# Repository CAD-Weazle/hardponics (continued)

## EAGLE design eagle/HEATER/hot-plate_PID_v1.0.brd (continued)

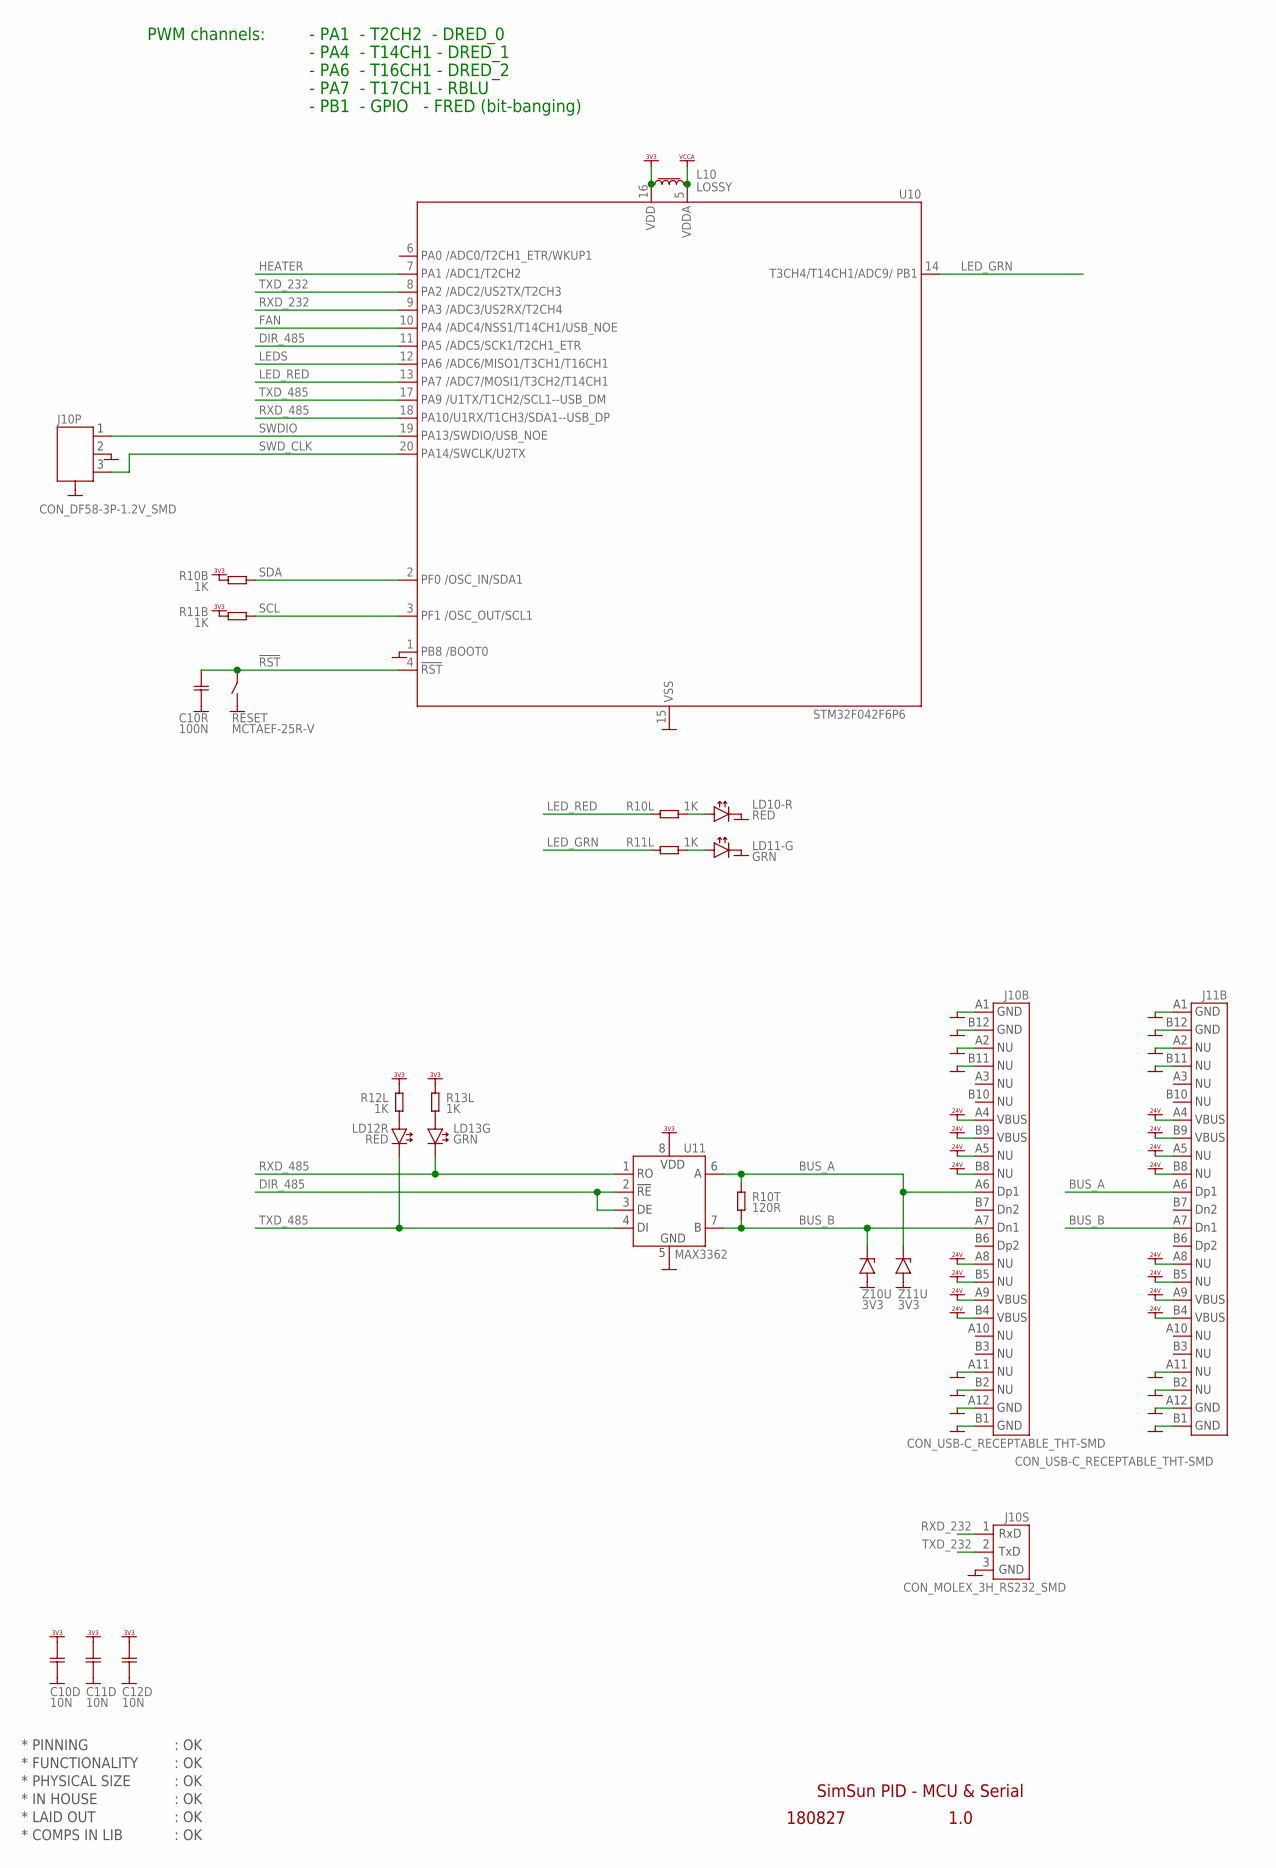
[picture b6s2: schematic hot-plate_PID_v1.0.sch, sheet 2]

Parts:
C10D, C11D, C12D: 10N; CAP0603
C10R: 100N; CAP0603
J10B, J11B: CON_USB-C_RECEPTABLE_THT-SMD
J10P: CON_DF58-3P-1.2V_SMD
J10S: CON_MOLEX_3H_RS232_SMD; CON_MOLEX_3H+SMD
L10: LOSSY; L_0603
LD10-R, LD12R: RED; LED_SMD_0603
LD11-G, LD13G: GRN; LED_SMD_0603
R10B, R10L, R11B, R11L, R12L, R13L: 1K; RES0603
R10T: 120R; RES0603
RESET: MCTAEF-25R-V; SWITCH_SMD_PBUTTON_2P
U10: STM32F042F6P6; TSSOP20
U11: MAX3362; SOT23-8
Z10U, Z11U: 3V3; ZENER_SOD80

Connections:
!RST: C10R.1, RESET.2 (3-4), U10.4 (4.!RST)
BUS_A: J10B.A6 (A6.DP1), J11B.A6 (A6.DP1), R10T.1, U11.6 (6.A), Z11U.2 (-)
BUS_B: J10B.A7 (A7.DN1), J11B.A7 (A7.DN1), R10T.2, U11.7 (7.B), Z10U.2 (-)
DIR_485: U10.11 (11.PA5), U11.2 (2.!RE), U11.3 (3.DE)
FAN: U10.10 (10.PA4); also elsewhere on the board
GND: C10D.2, C10R.2, C11D.2, C12D.2, J10B.A1 (A1.GND), J10B.A2 (A2.NU), J10B.A11 (A11.NU), J10B.A12 (A12.GND), J10B.B1 (B1.GND), J10B.B2 (B2.NU), J10B.B11 (B11.NU), J10B.B12 (B12.GND), J10P.2, J10P.GND1 (4), J10P.GND2 (4), J10S.3, J11B.A1 (A1.GND), J11B.A2 (A2.NU), J11B.A11 (A11.NU), J11B.A12 (A12.GND), J11B.B1 (B1.GND), J11B.B2 (B2.NU), J11B.B11 (B11.NU), J11B.B12 (B12.GND), LD10-R.C, LD11-G.C, RESET.1 (1-2), U10.1 (1.BOOT0), U10.15 (15.GND), U11.5 (5.GND), Z10U.1 (+), Z11U.1 (+); also elsewhere on the board
HEATER: U10.7 (7.PA1); also elsewhere on the board
LEDS: U10.12 (12.PA6); also elsewhere on the board
LED_GRN: R11L.1, U10.14 (14.PB1)
LED_RED: R10L.1, U10.13 (13.PA7)
unnamed: LD11-G.A, R11L.2
unnamed: LD10-R.A, R10L.2
unnamed: LD13G.A, R13L.2
unnamed: LD12R.A, R12L.2
RXD_232: J10S.1, U10.9 (9.PA3)
RXD_485: LD13G.C, U10.18 (18.PA10), U11.1 (1.RO)
SCL: R11B.2, U10.3 (3.OSC_OUT); also elsewhere on the board
SDA: R10B.2, U10.2 (2.OSC_IN); also elsewhere on the board
SWDIO: J10P.1, U10.19 (19.PA13)
SWD_CLK: J10P.3, U10.20 (20.PA14)
TXD_232: J10S.2, U10.8 (8.PA2)
TXD_485: LD12R.C, U10.17 (17.PA9), U11.4 (4.DI)
VCCA: L10.2, U10.5 (5.VDDA)
VDD_3V3: C10D.1, C11D.1, C12D.1, L10.1, R10B.1, R11B.1, R12L.1, R13L.1, U10.16 (16.VDD), U11.8 (8.VDD); also elsewhere on the board
VDD_24V: J10B.A4 (A4.VBUS), J10B.A5 (A5.NU), J10B.A8 (A8.NU), J10B.A9 (A9.VBUS), J10B.B4 (B4.VBUS), J10B.B5 (B5.NU), J10B.B8 (B8.NU), J10B.B9 (B9.VBUS), J11B.A4 (A4.VBUS), J11B.A5 (A5.NU), J11B.A8 (A8.NU), J11B.A9 (A9.VBUS), J11B.B4 (B4.VBUS), J11B.B5 (B5.NU), J11B.B8 (B8.NU), J11B.B9 (B9.VBUS); also elsewhere on the board

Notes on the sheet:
* PINNING
* FUNCTIONALITY
* PHYSICAL SIZE
* LAID OUT
* COMPS IN LIB
* IN HOUSE
: OK
SimSun PID - MCU & Serial
180827
1.0
PWM channels:
- PA1 - T2CH2 - DRED_0
- PA4 - T14CH1 - DRED_1
- PA6 - T16CH1 - DRED_2
- PA7 - T17CH1 - RBLU
- PB1 - GPIO - FRED (bit-banging)

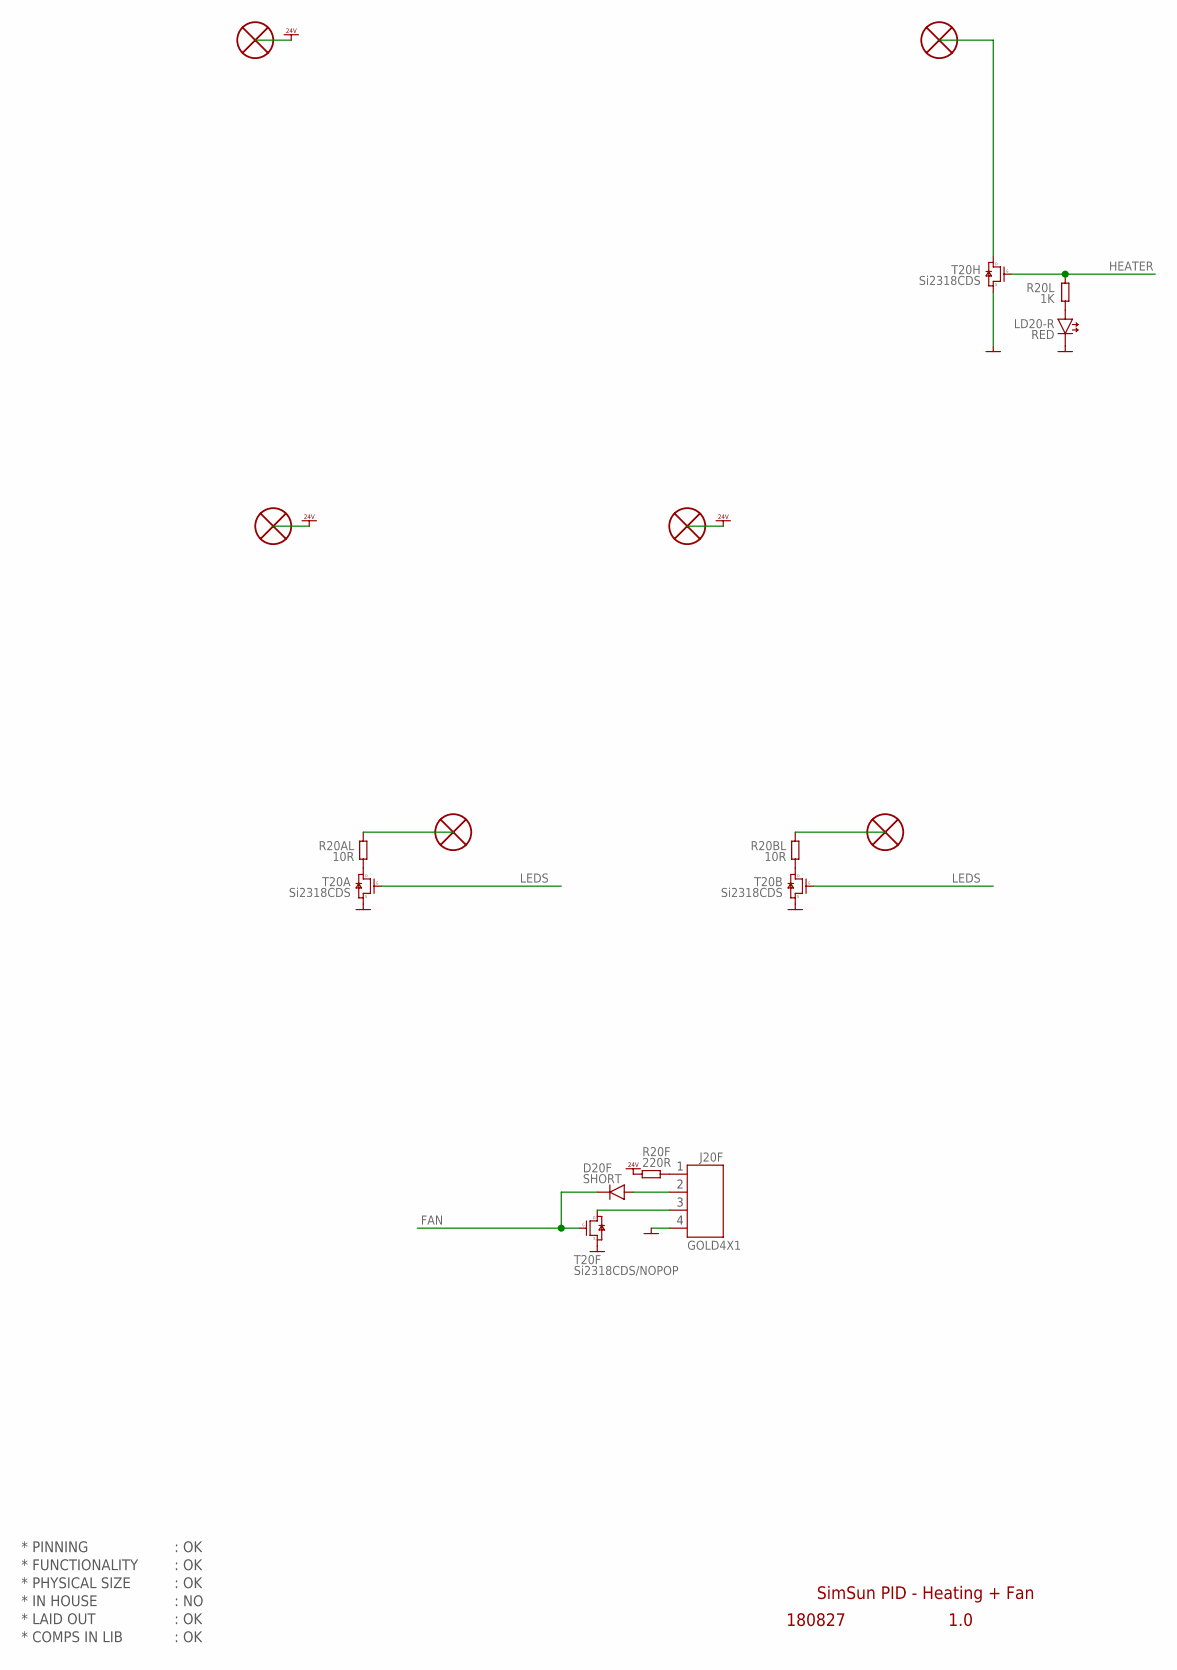
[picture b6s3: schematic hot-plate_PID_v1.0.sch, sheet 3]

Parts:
D20F: SHORT; DIODE_SOD323
H5, H6, H10, H15, H16, H17: HOLE_PTH_1.0MM
J20F: GOLD4X1
LD20-R: RED; LED_SMD_0603
R20AL, R20BL: 10R; RES0603
R20F: 220R; RES0603
R20L: 1K; RES0603
T20A, T20B, T20H: Si2318CDS; NFET_SOT23
T20F: Si2318CDS/NOPOP; NFET_SOT23

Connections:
FAN: D20F.1- (-), T20F.1 (G1); also elsewhere on the board
GND: J20F.4, LD20-R.C, T20A.2 (S2), T20B.2 (S2), T20F.2 (S2), T20H.2 (S2); also elsewhere on the board
HEATER: R20L.1, T20H.1 (G1); also elsewhere on the board
LEDS: T20A.1 (G1), T20B.1 (G1); also elsewhere on the board
unnamed: J20F.1, R20F.1
unnamed: H5.1, T20H.3 (D3)
unnamed: LD20-R.A, R20L.2
unnamed: H16.1, R20BL.1
unnamed: H17.1, R20AL.1
unnamed: R20AL.2, T20A.3 (D3)
unnamed: R20BL.2, T20B.3 (D3)
unnamed: J20F.3, T20F.3 (D3)
unnamed: D20F.2 (+), J20F.2
VDD_24V: H6.1, H10.1, H15.1, R20F.2; also elsewhere on the board

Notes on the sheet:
* PINNING
* FUNCTIONALITY
* PHYSICAL SIZE
* LAID OUT
* COMPS IN LIB
* IN HOUSE
: OK
SimSun PID - Heating + Fan
1.0
180827
: NO

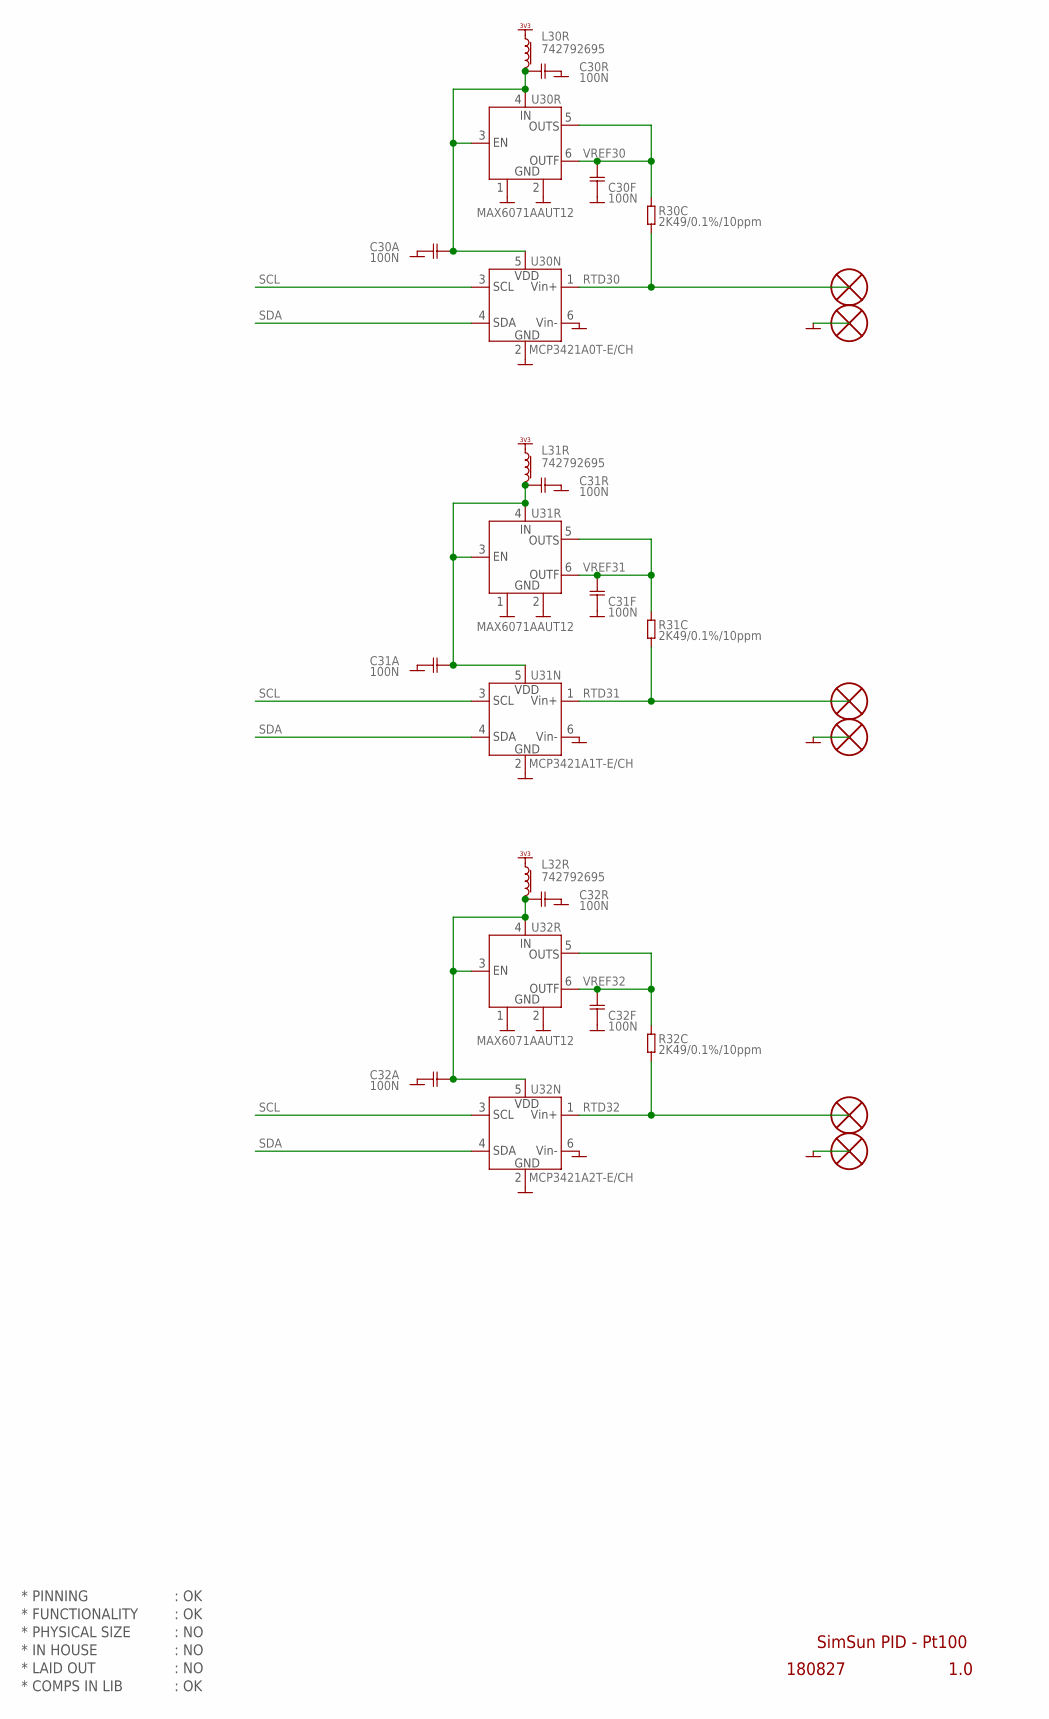
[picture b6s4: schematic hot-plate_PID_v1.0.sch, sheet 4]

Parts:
C30A, C30F, C30R, C31A, C31F, C31R, C32A, C32F, C32R: 100N; CAP0603
H7, H8, H11, H12, H13, H14: HOLE_PTH_1.0MM
L30R, L31R, L32R: 742792695; L_0603
R30C, R31C, R32C: 2K49/0.1%/10ppm; RES0603
U30N: MCP3421A0T-E/CH; SOT23-6
U30R, U31R, U32R: MAX6071AAUT12; SOT23-6
U31N: MCP3421A1T-E/CH; SOT23-6
U32N: MCP3421A2T-E/CH; SOT23-6

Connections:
GND: C30A.1, C30F.1, C30R.1, C31A.1, C31F.1, C31R.1, C32A.1, C32F.1, C32R.1, H8.1, H12.1, H14.1, U30N.2 (2.VSS), U30N.6 (6.VIN-), U30R.1 (1.GND), U30R.2 (2.GND), U31N.2 (2.VSS), U31N.6 (6.VIN-), U31R.1 (1.GND), U31R.2 (2.GND), U32N.2 (2.VSS), U32N.6 (6.VIN-), U32R.1 (1.GND), U32R.2 (2.GND); also elsewhere on the board
unnamed: C31A.2, C31R.2, L31R.2, U31N.5 (5.VDD), U31R.3 (3.EN), U31R.4 (4.IN)
unnamed: C32A.2, C32R.2, L32R.2, U32N.5 (5.VDD), U32R.3 (3.EN), U32R.4 (4.IN)
unnamed: C30A.2, C30R.2, L30R.2, U30N.5 (5.VDD), U30R.3 (3.EN), U30R.4 (4.IN)
RTD30: H7.1, R30C.2, U30N.1 (1.VIN+)
RTD31: H11.1, R31C.2, U31N.1 (1.VIN+)
RTD32: H13.1, R32C.2, U32N.1 (1.VIN+)
SCL: U30N.3 (3.SCL), U31N.3 (3.SCL), U32N.3 (3.SCL); also elsewhere on the board
SDA: U30N.4 (4.SDA), U31N.4 (4.SDA), U32N.4 (4.SDA); also elsewhere on the board
VDD_3V3: L30R.1, L31R.1, L32R.1; also elsewhere on the board
VREF30: C30F.2, R30C.1, U30R.5 (5.OUTS), U30R.6 (6.OUTF)
VREF31: C31F.2, R31C.1, U31R.5 (5.OUTS), U31R.6 (6.OUTF)
VREF32: C32F.2, R32C.1, U32R.5 (5.OUTS), U32R.6 (6.OUTF)

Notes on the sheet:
* PINNING
* FUNCTIONALITY
* PHYSICAL SIZE
* LAID OUT
* COMPS IN LIB
* IN HOUSE
: OK
1.0
180827
SimSun PID - Pt100
: NO

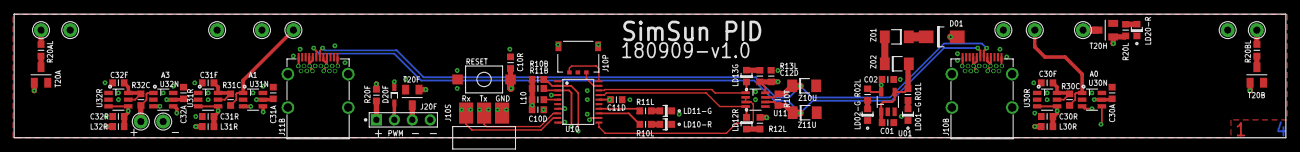
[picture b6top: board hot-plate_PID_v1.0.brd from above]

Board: 4 copper layers, 180.0 x 17.5 mm, 79 parts (0 on the bottom side), 48 nets.

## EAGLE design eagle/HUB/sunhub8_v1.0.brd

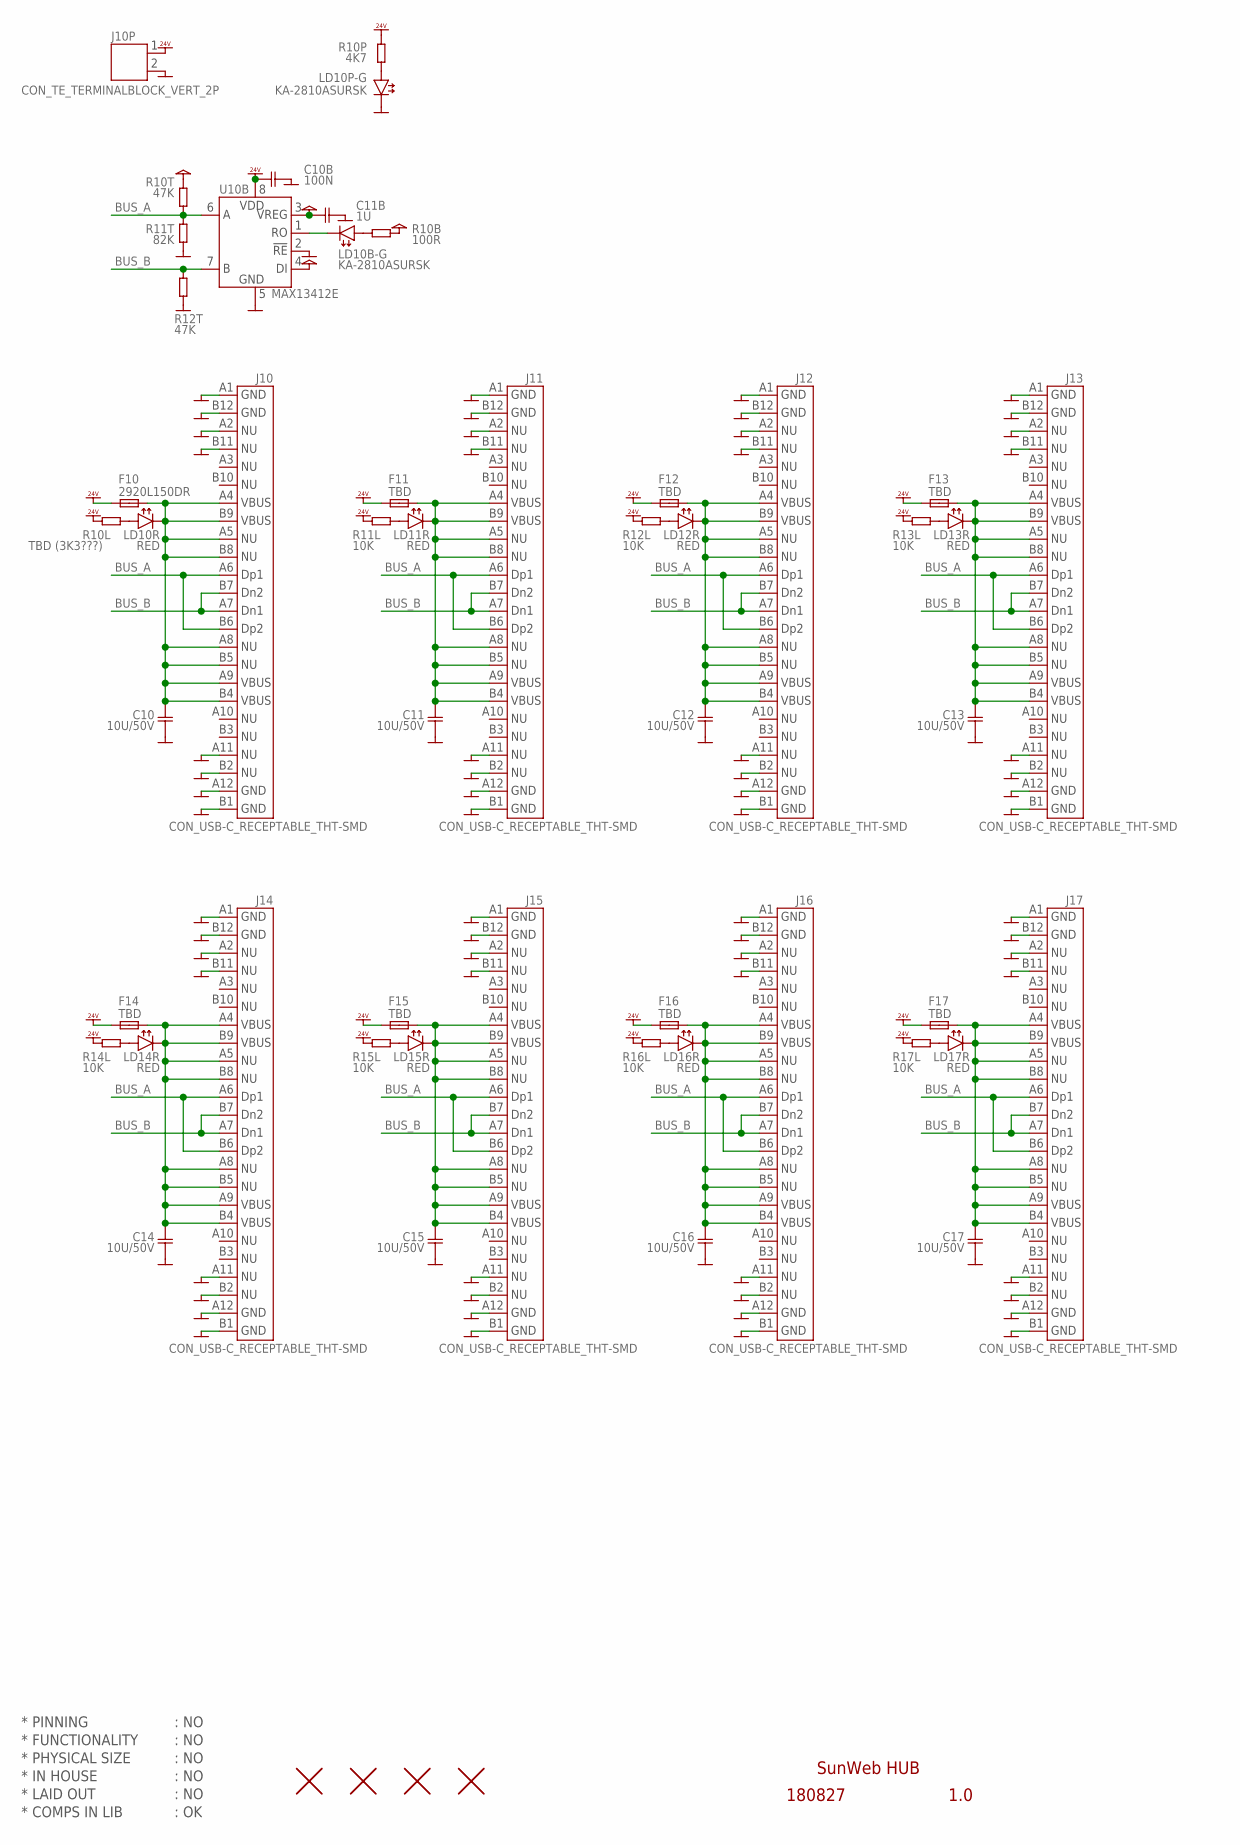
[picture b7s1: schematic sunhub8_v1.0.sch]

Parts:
C10, C11, C12, C13, C14, C15, C16, C17: 10U/50V; CAP1206
C10B: 100N; CAP0603
C11B: 1U; CAP0603
F10: 2920L150DR; POLYFUSE2920
F11, F12, F13, F14, F15, F16, F17: TBD; POLYFUSE2920
H1, H2, H3, H4: HOLE_NPTH_3.2MM
J10, J11, J12, J13, J14, J15, J16, J17: CON_USB-C_RECEPTABLE_THT-SMD
J10P: CON_TE_TERMINALBLOCK_VERT_2P
LD10B-G, LD10P-G: KA-2810ASURSK; LED_SMD_ANGLE
LD10R, LD11R, LD12R, LD13R, LD14R, LD15R, LD16R, LD17R: RED; LED_SMD_ANGLE
R10B: 100R; RES0603
R10L: TBD (3K3???); RES0603
R10P: 4K7; RES0603
R10T, R12T: 47K; RES0603
R11L, R12L, R13L, R14L, R15L, R16L, R17L: 10K; RES0603
R11T: 82K; RES0603
U10B: MAX13412E; SO8

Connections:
BUS_A: J10.A6 (A6.DP1), J10.B6 (B6.DP2), J11.A6 (A6.DP1), J11.B6 (B6.DP2), J12.A6 (A6.DP1), J12.B6 (B6.DP2), J13.A6 (A6.DP1), J13.B6 (B6.DP2), J14.A6 (A6.DP1), J14.B6 (B6.DP2), J15.A6 (A6.DP1), J15.B6 (B6.DP2), J16.A6 (A6.DP1), J16.B6 (B6.DP2), J17.A6 (A6.DP1), J17.B6 (B6.DP2), R10T.2, R11T.1, U10B.6 (6.A)
BUS_B: J10.A7 (A7.DN1), J10.B7 (B7.DN2), J11.A7 (A7.DN1), J11.B7 (B7.DN2), J12.A7 (A7.DN1), J12.B7 (B7.DN2), J13.A7 (A7.DN1), J13.B7 (B7.DN2), J14.A7 (A7.DN1), J14.B7 (B7.DN2), J15.A7 (A7.DN1), J15.B7 (B7.DN2), J16.A7 (A7.DN1), J16.B7 (B7.DN2), J17.A7 (A7.DN1), J17.B7 (B7.DN2), R12T.1, U10B.7 (7.B)
GND: C10.2, C10B.2, C11.2, C11B.2, C12.2, C13.2, C14.2, C15.2, C16.2, C17.2, J10.A1 (A1.GND), J10.A2 (A2.NU), J10.A11 (A11.NU), J10.A12 (A12.GND), J10.B1 (B1.GND), J10.B2 (B2.NU), J10.B11 (B11.NU), J10.B12 (B12.GND), J10P.2, J11.A1 (A1.GND), J11.A2 (A2.NU), J11.A11 (A11.NU), J11.A12 (A12.GND), J11.B1 (B1.GND), J11.B2 (B2.NU), J11.B11 (B11.NU), J11.B12 (B12.GND), J12.A1 (A1.GND), J12.A2 (A2.NU), J12.A11 (A11.NU), J12.A12 (A12.GND), J12.B1 (B1.GND), J12.B2 (B2.NU), J12.B11 (B11.NU), J12.B12 (B12.GND), J13.A1 (A1.GND), J13.A2 (A2.NU), J13.A11 (A11.NU), J13.A12 (A12.GND), J13.B1 (B1.GND), J13.B2 (B2.NU), J13.B11 (B11.NU), J13.B12 (B12.GND), J14.A1 (A1.GND), J14.A2 (A2.NU), J14.A11 (A11.NU), J14.A12 (A12.GND), J14.B1 (B1.GND), J14.B2 (B2.NU), J14.B11 (B11.NU), J14.B12 (B12.GND), J15.A1 (A1.GND), J15.A2 (A2.NU), J15.A11 (A11.NU), J15.A12 (A12.GND), J15.B1 (B1.GND), J15.B2 (B2.NU), J15.B11 (B11.NU), J15.B12 (B12.GND), J16.A1 (A1.GND), J16.A2 (A2.NU), J16.A11 (A11.NU), J16.A12 (A12.GND), J16.B1 (B1.GND), J16.B2 (B2.NU), J16.B11 (B11.NU), J16.B12 (B12.GND), J17.A1 (A1.GND), J17.A2 (A2.NU), J17.A11 (A11.NU), J17.A12 (A12.GND), J17.B1 (B1.GND), J17.B2 (B2.NU), J17.B11 (B11.NU), J17.B12 (B12.GND), LD10P-G.C, R11T.2, R12T.2, U10B.2 (2.!RE), U10B.5 (5.GND)
unnamed: C10.1, F10.2, J10.A4 (A4.VBUS), J10.A5 (A5.NU), J10.A8 (A8.NU), J10.A9 (A9.VBUS), J10.B4 (B4.VBUS), J10.B5 (B5.NU), J10.B8 (B8.NU), J10.B9 (B9.VBUS), LD10R.C
unnamed: C11.1, F11.2, J11.A4 (A4.VBUS), J11.A5 (A5.NU), J11.A8 (A8.NU), J11.A9 (A9.VBUS), J11.B4 (B4.VBUS), J11.B5 (B5.NU), J11.B8 (B8.NU), J11.B9 (B9.VBUS), LD11R.C
unnamed: LD11R.A, R11L.2
unnamed: C12.1, F12.2, J12.A4 (A4.VBUS), J12.A5 (A5.NU), J12.A8 (A8.NU), J12.A9 (A9.VBUS), J12.B4 (B4.VBUS), J12.B5 (B5.NU), J12.B8 (B8.NU), J12.B9 (B9.VBUS), LD12R.C
unnamed: C13.1, F13.2, J13.A4 (A4.VBUS), J13.A5 (A5.NU), J13.A8 (A8.NU), J13.A9 (A9.VBUS), J13.B4 (B4.VBUS), J13.B5 (B5.NU), J13.B8 (B8.NU), J13.B9 (B9.VBUS), LD13R.C
unnamed: C14.1, F14.2, J14.A4 (A4.VBUS), J14.A5 (A5.NU), J14.A8 (A8.NU), J14.A9 (A9.VBUS), J14.B4 (B4.VBUS), J14.B5 (B5.NU), J14.B8 (B8.NU), J14.B9 (B9.VBUS), LD14R.C
unnamed: C15.1, F15.2, J15.A4 (A4.VBUS), J15.A5 (A5.NU), J15.A8 (A8.NU), J15.A9 (A9.VBUS), J15.B4 (B4.VBUS), J15.B5 (B5.NU), J15.B8 (B8.NU), J15.B9 (B9.VBUS), LD15R.C
unnamed: C16.1, F16.2, J16.A4 (A4.VBUS), J16.A5 (A5.NU), J16.A8 (A8.NU), J16.A9 (A9.VBUS), J16.B4 (B4.VBUS), J16.B5 (B5.NU), J16.B8 (B8.NU), J16.B9 (B9.VBUS), LD16R.C
unnamed: C17.1, F17.2, J17.A4 (A4.VBUS), J17.A5 (A5.NU), J17.A8 (A8.NU), J17.A9 (A9.VBUS), J17.B4 (B4.VBUS), J17.B5 (B5.NU), J17.B8 (B8.NU), J17.B9 (B9.VBUS), LD17R.C
unnamed: LD10R.A, R10L.2
unnamed: LD12R.A, R12L.2
unnamed: LD13R.A, R13L.2
unnamed: LD14R.A, R14L.2
unnamed: LD15R.A, R15L.2
unnamed: LD16R.A, R16L.2
unnamed: LD17R.A, R17L.2
unnamed: LD10B-G.A, R10B.1
unnamed: LD10B-G.C, U10B.1 (1.RO)
unnamed: LD10P-G.A, R10P.2
VCC: C11B.1, R10B.2, R10T.1, U10B.3 (3.DE), U10B.4 (4.DI)
VDD_24V: C10B.1, F10.1, F11.1, F12.1, F13.1, F14.1, F15.1, F16.1, F17.1, J10P.1, R10L.1, R10P.1, R11L.1, R12L.1, R13L.1, R14L.1, R15L.1, R16L.1, R17L.1, U10B.8 (8.VDD)

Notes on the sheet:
* PINNING
* FUNCTIONALITY
* PHYSICAL SIZE
* LAID OUT
* COMPS IN LIB
* IN HOUSE
: NO
: OK
SunWeb HUB
180827
1.0

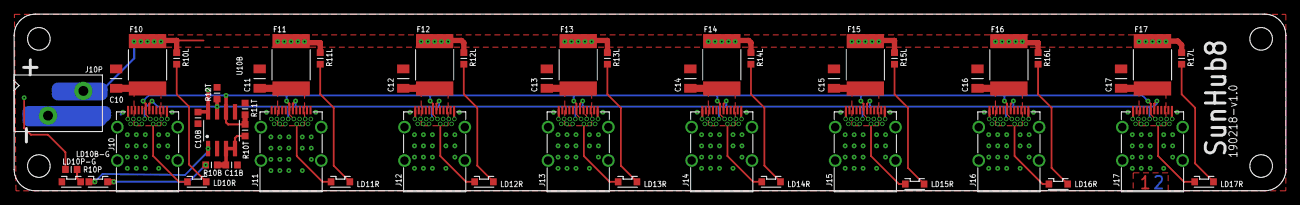
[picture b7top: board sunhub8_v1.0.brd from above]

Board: 2 copper layers, 180.0 x 25.0 mm, 55 parts (0 on the bottom side), 24 nets.

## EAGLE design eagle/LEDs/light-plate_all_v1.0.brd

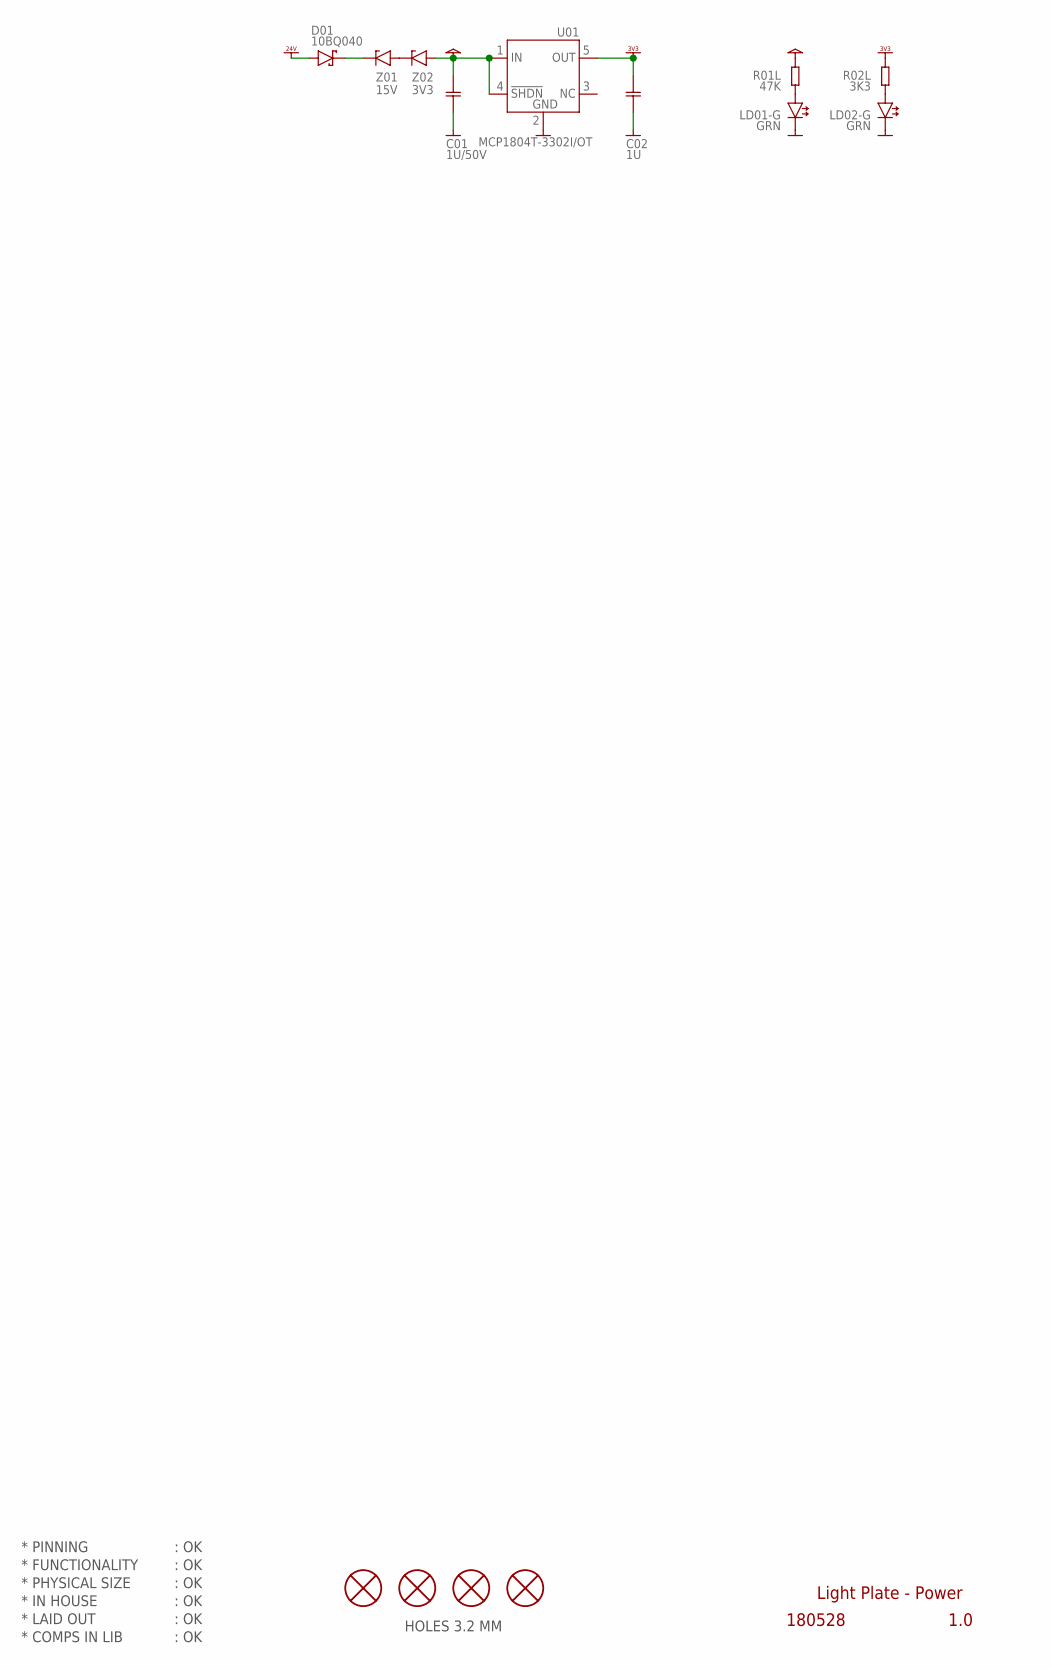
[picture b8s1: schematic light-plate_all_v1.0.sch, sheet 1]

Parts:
C01: 1U/50V; CAP0603
C02: 1U; CAP0603
D01: 10BQ040; DIODE_SMA
H1, H2, H3, H4: HOLE_3.2MM; HOLE_PTH_3.2MM
LD01-G, LD02-G: GRN; LED_SMD_0603
R01L: 47K; RES0603
R02L: 3K3; RES0603
U01: MCP1804T-3302I/OT; SOT23-5
Z01: 15V; ZENER_SOD80
Z02: 3V3; ZENER_SOD80

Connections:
GND: C01.2, C02.2, LD01-G.C, LD02-G.C, U01.2 (2.GND); also elsewhere on the board
unnamed: LD02-G.A, R02L.2
unnamed: LD01-G.A, R01L.2
unnamed: D01.C (-), Z01.2 (-)
unnamed: Z01.1 (+), Z02.2 (-)
VCC: C01.1, R01L.1, U01.1 (1.IN), U01.4 (4.SHDN), Z02.1 (+)
VDD_3V3: C02.1, R02L.1, U01.5 (5.OUT); also elsewhere on the board
VDD_24V: D01.A (+); also elsewhere on the board

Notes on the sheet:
* PINNING
* FUNCTIONALITY
* PHYSICAL SIZE
* LAID OUT
* COMPS IN LIB
* IN HOUSE
HOLES 3.2 MM
Light Plate - Power
180528
1.0
: OK

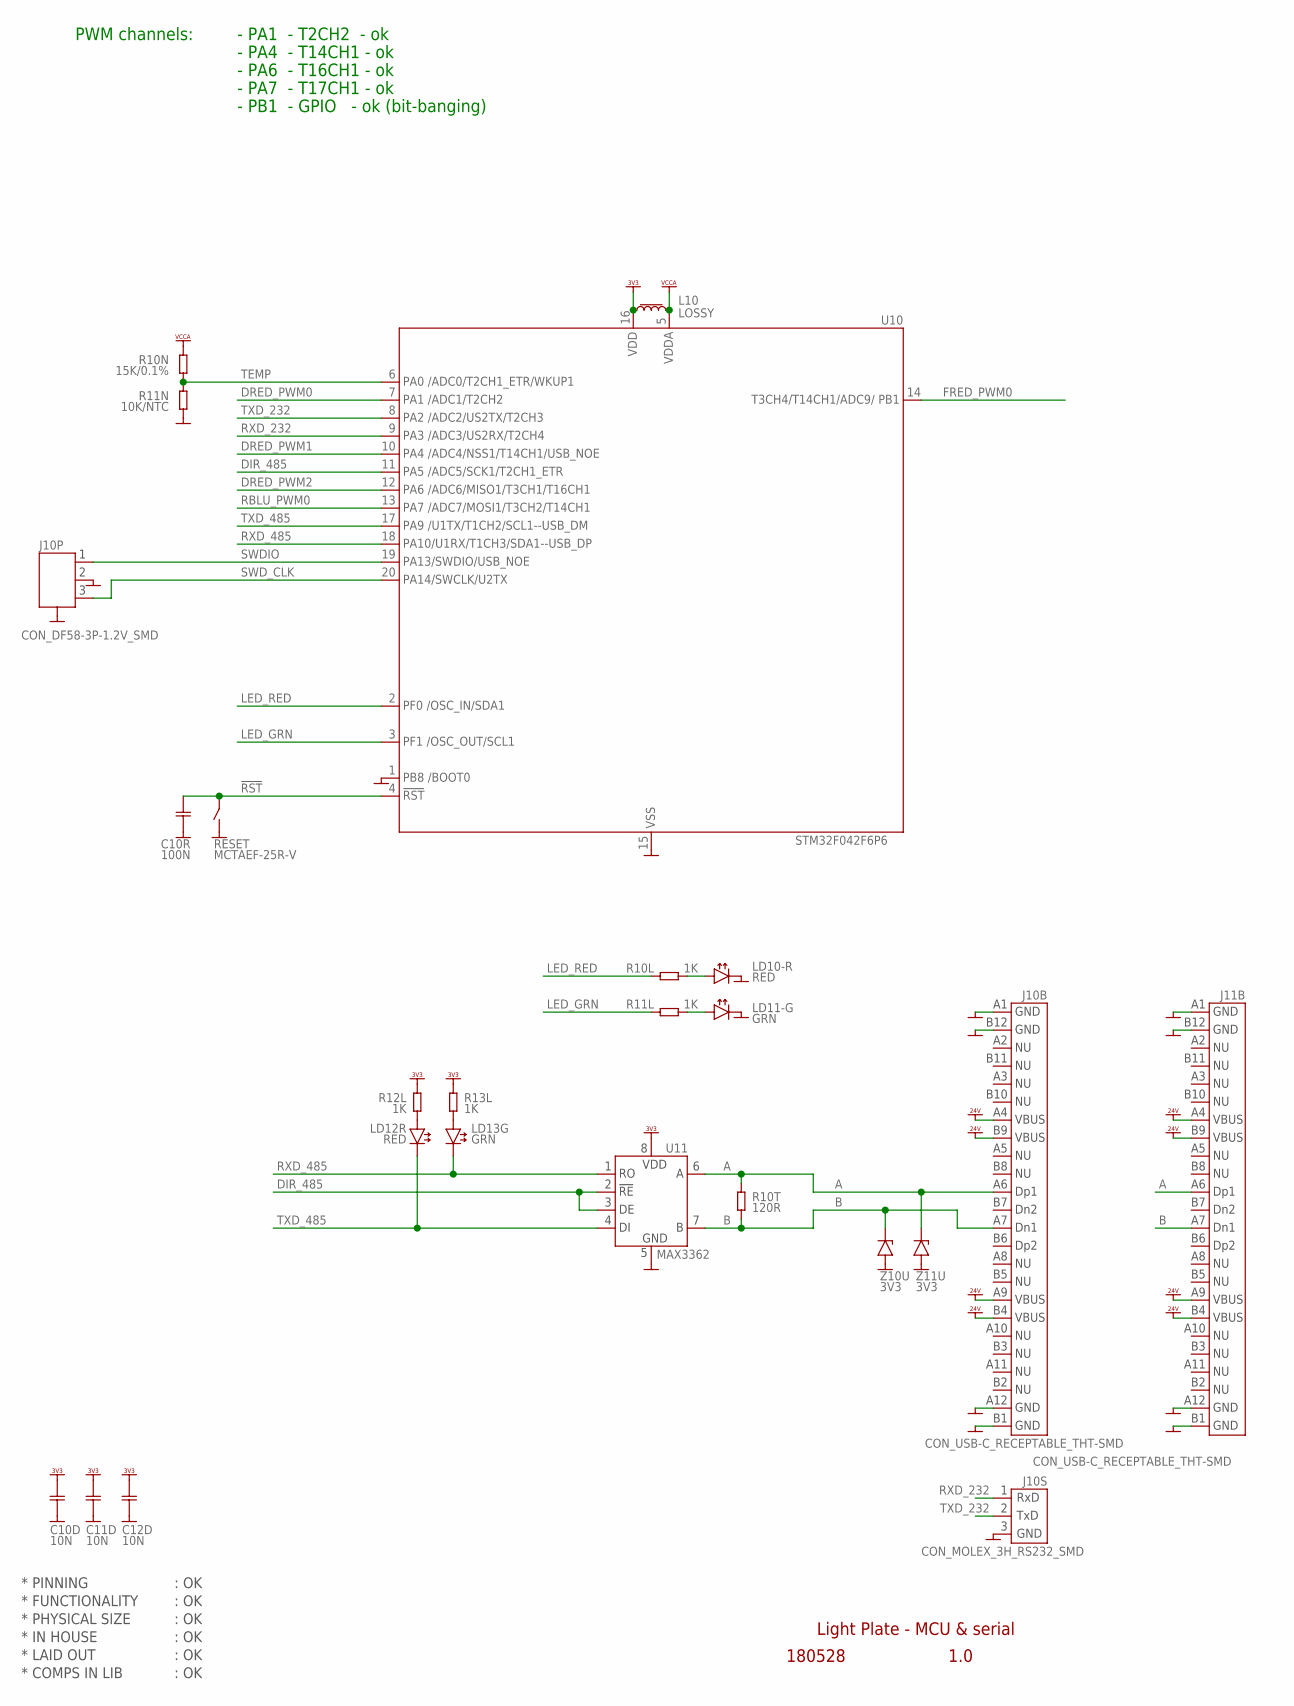
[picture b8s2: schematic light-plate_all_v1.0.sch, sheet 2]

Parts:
C10D, C11D, C12D: 10N; CAP0603
C10R: 100N; CAP0603
J10B, J11B: CON_USB-C_RECEPTABLE_THT-SMD
J10P: CON_DF58-3P-1.2V_SMD
J10S: CON_MOLEX_3H_RS232_SMD; CON_MOLEX_3H+SMD
L10: LOSSY; L_0603
LD10-R, LD12R: RED; LED_SMD_0603
LD11-G, LD13G: GRN; LED_SMD_0603
R10L, R11L, R12L, R13L: 1K; RES0603
R10N: 15K/0.1%; RES0603
R10T: 120R; RES0603
R11N: 10K/NTC; RES0603
RESET: MCTAEF-25R-V; SWITCH_SMD_PBUTTON_2P
U10: STM32F042F6P6; TSSOP20
U11: MAX3362; SOT23-8
Z10U, Z11U: 3V3; ZENER_SOD80

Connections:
!RST: C10R.1, RESET.2 (3-4), U10.4 (4.!RST)
A: J10B.A6 (A6.DP1), J11B.A6 (A6.DP1), R10T.1, U11.6 (6.A), Z11U.2 (-)
B: J10B.A7 (A7.DN1), J11B.A7 (A7.DN1), R10T.2, U11.7 (7.B), Z10U.2 (-)
DIR_485: U10.11 (11.PA5), U11.2 (2.!RE), U11.3 (3.DE)
DRED_PWM0: U10.7 (7.PA1); also elsewhere on the board
DRED_PWM1: U10.10 (10.PA4); also elsewhere on the board
DRED_PWM2: U10.12 (12.PA6); also elsewhere on the board
FRED_PWM0: U10.14 (14.PB1); also elsewhere on the board
GND: C10D.2, C10R.2, C11D.2, C12D.2, J10B.A1 (A1.GND), J10B.A12 (A12.GND), J10B.B1 (B1.GND), J10B.B12 (B12.GND), J10P.2, J10P.GND1 (4), J10P.GND2 (4), J10S.3, J11B.A1 (A1.GND), J11B.A12 (A12.GND), J11B.B1 (B1.GND), J11B.B12 (B12.GND), LD10-R.C, LD11-G.C, R11N.1, RESET.1 (1-2), U10.1 (1.BOOT0), U10.15 (15.GND), U11.5 (5.GND), Z10U.1 (+), Z11U.1 (+); also elsewhere on the board
LED_GRN: R11L.1, U10.3 (3.OSC_OUT)
LED_RED: R10L.1, U10.2 (2.OSC_IN)
unnamed: LD11-G.A, R11L.2
unnamed: LD10-R.A, R10L.2
unnamed: LD13G.A, R13L.2
unnamed: LD12R.A, R12L.2
RBLU_PWM0: U10.13 (13.PA7); also elsewhere on the board
RXD_232: J10S.1, U10.9 (9.PA3)
RXD_485: LD13G.C, U10.18 (18.PA10), U11.1 (1.RO)
SWDIO: J10P.1, U10.19 (19.PA13)
SWD_CLK: J10P.3, U10.20 (20.PA14)
TEMP: R10N.1, R11N.2, U10.6 (6.PA0)
TXD_232: J10S.2, U10.8 (8.PA2)
TXD_485: LD12R.C, U10.17 (17.PA9), U11.4 (4.DI)
VCCA: L10.2, R10N.2, U10.5 (5.VDDA)
VDD_3V3: C10D.1, C11D.1, C12D.1, L10.1, R12L.1, R13L.1, U10.16 (16.VDD), U11.8 (8.VDD); also elsewhere on the board
VDD_24V: J10B.A4 (A4.VBUS), J10B.A9 (A9.VBUS), J10B.B4 (B4.VBUS), J10B.B9 (B9.VBUS), J11B.A4 (A4.VBUS), J11B.A9 (A9.VBUS), J11B.B4 (B4.VBUS), J11B.B9 (B9.VBUS); also elsewhere on the board

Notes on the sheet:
* PINNING
* FUNCTIONALITY
* PHYSICAL SIZE
* LAID OUT
* COMPS IN LIB
* IN HOUSE
: OK
Light Plate - MCU & serial
180528
1.0
PWM channels:
- PA1 - T2CH2 - ok
- PA4 - T14CH1 - ok
- PA6 - T16CH1 - ok
- PA7 - T17CH1 - ok
- PB1 - GPIO - ok (bit-banging)
